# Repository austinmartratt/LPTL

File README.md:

# LPTL
Low Power Temperature Logger - Bluetooth Low Energy

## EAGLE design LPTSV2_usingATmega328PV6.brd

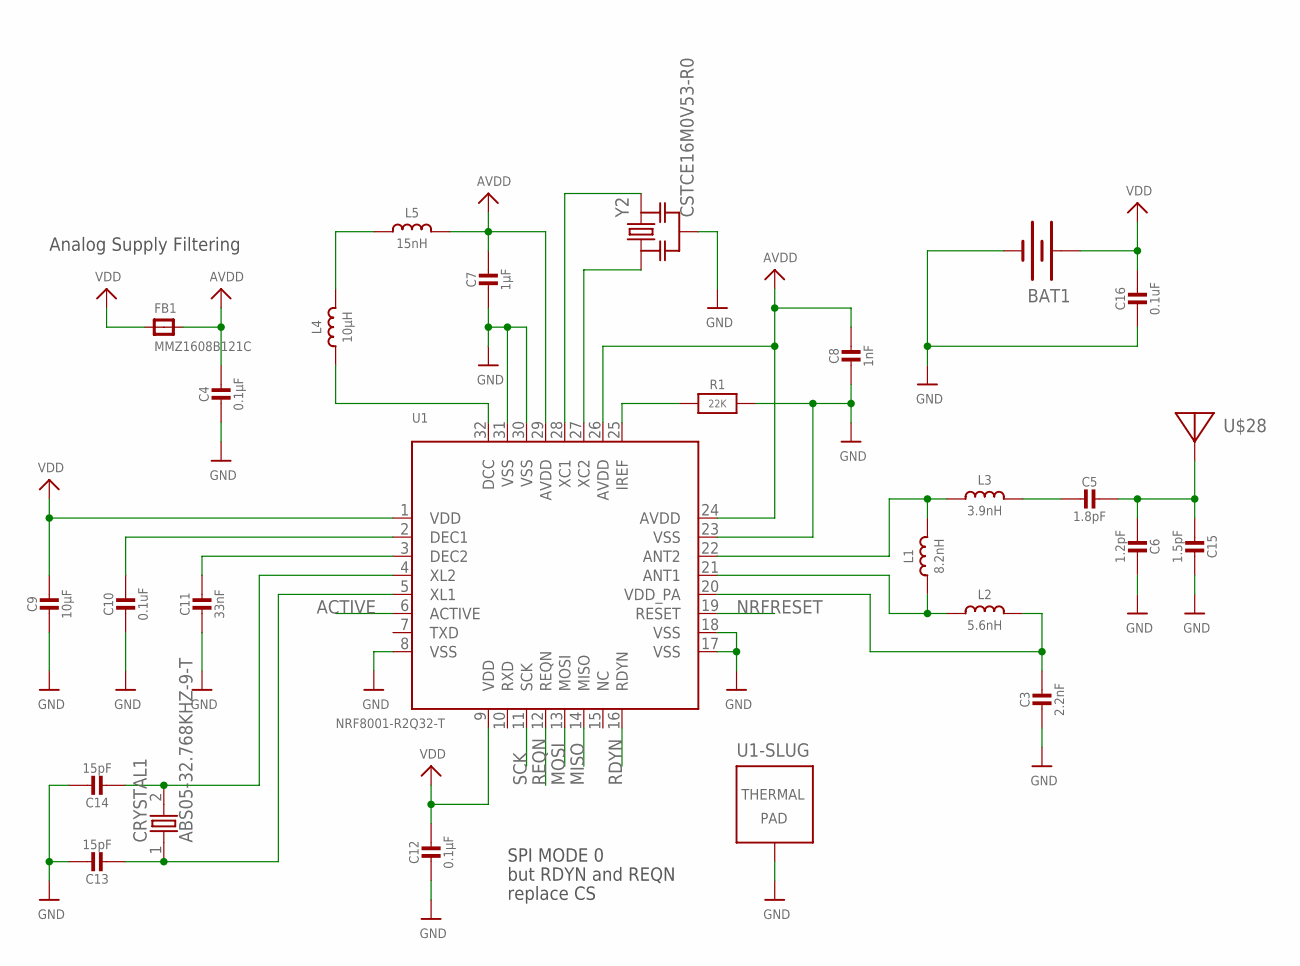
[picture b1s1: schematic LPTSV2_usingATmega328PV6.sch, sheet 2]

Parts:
BAT1: LINX-BAT-HLD-00120SMD; BATTCON_20MM; PARTNUMBER BAT-HLD-001-TRCT-ND
C3: 2.2nF; _0402; PARTNUMBER C0402C222J8JAC7867
C4, C12: 0.1µF; _0402; PARTNUMBER GRM155R71C104KA88J
C5: 1.8pF; _0402MP; PARTNUMBER GRM1555C1E1R8BA01D
C6: 1.2pF; _0402MP; PARTNUMBER GRM1555C1E1R2BA01D
C7: 1µF; _0402; PARTNUMBER 0402ZD105KAT2A
C8: 1nF; _0402; PARTNUMBER GRM155R71H102KA01D
C9: 10µF; _0402; PARTNUMBER GRM155R60J106ME15D
C10, C16: 0.1uF; _0402; PARTNUMBER GRM155R71C104KA88J
C11: 33nF; _0402; PARTNUMBER C0402C333K8RACTU
C13, C14: 15pF; _0402; PARTNUMBER GRM1555C1H150JA01D
C15: 1.5pF; _0402MP; PARTNUMBER GRM1555C1H1R5BA01D
CRYSTAL1: ABS05-32.768KHZ-9-T; CRYSTAL-2PIN
FB1: MMZ1608B121C; 0805; PARTNUMBER MMZ1608B121CTDH5
L1: 8.2nH; _0402; PARTNUMBER LQP15MN8N2B02D
L2: 5.6nH; _0402; PARTNUMBER LQP15MN5N6B02D
L3: 3.9nH; _0402; PARTNUMBER LQP03TN3N9B02D
L4: 10µH; _0603; PARTNUMBER LBMF1608T100K
L5: 15nH; _0603; PARTNUMBER L-14C15NJV4T
R1: 22K; _0805; PARTNUMBER RC0805JR-0722KL
U1: NRF8001-R2Q32-T; MICROBUILDER_QFN32_5MM
U$28: ANTENNA_PCBNRF8001_1.6MM; ANT_PCB_2.4GHZ_NRF8001_1.6MM_1OZ
Y2: CSTCE16M0V53-R0; RESONATOR_MURATA2

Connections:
ACTIVE: U1.6 (ACTIVE)
AVDD: C4.1, C7.1, C8.1, FB1.2, L5.2, U1.24 (AVDD), U1.26 (AVDD), U1.29 (AVDD)
GND: BAT1.2 (-), C3.2, C4.2, C6.1, C7.2, C8.2, C9.2, C10.2, C11.2, C12.2, C13.1, C14.1, C15.1, C16.2, R1.2, U1.8 (VSS), U1.17 (VSS), U1.18 (VSS), U1.23 (VSS), U1.30 (VSS), U1.31 (VSS), U1.33 (TP), Y2.2; also elsewhere on the board
MISO: U1.14 (MISO); also elsewhere on the board
MOSI: U1.13 (MOSI); also elsewhere on the board
unnamed: L1.2, L3.1, U1.22 (ANT2)
unnamed: L1.1, L2.1, U1.21 (ANT1)
unnamed: C3.1, L2.2, U1.20 (VDD_PA)
unnamed: L4.2, L5.1
unnamed: C5.2, L3.2
unnamed: C11.1, U1.3 (DEC2)
unnamed: C10.1, U1.2 (DEC1)
unnamed: U1.28 (XC1), Y2.3
unnamed: U1.27 (XC2), Y2.1
unnamed: L4.1, U1.32 (DCC)
unnamed: R1.1, U1.25 (IREF)
unnamed: C5.1, C6.2, C15.2, U$28.FEED
unnamed: C14.2, CRYSTAL1.2, U1.4 (XL2)
unnamed: C13.2, CRYSTAL1.1, U1.5 (XL1)
NRFRESET: U1.19 (RESET); also elsewhere on the board
RDYN: U1.16 (RDYN); also elsewhere on the board
REQN: U1.12 (REQN); also elsewhere on the board
SCK: U1.11 (SCK); also elsewhere on the board
VDD: BAT1.1 (+), BAT1.3 (+), C9.1, C12.1, C16.1, FB1.1, U1.1 (VDD), U1.9 (VDD); also elsewhere on the board

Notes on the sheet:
Analog Supply Filtering
SPI MODE 0
but RDYN and REQN
replace CS

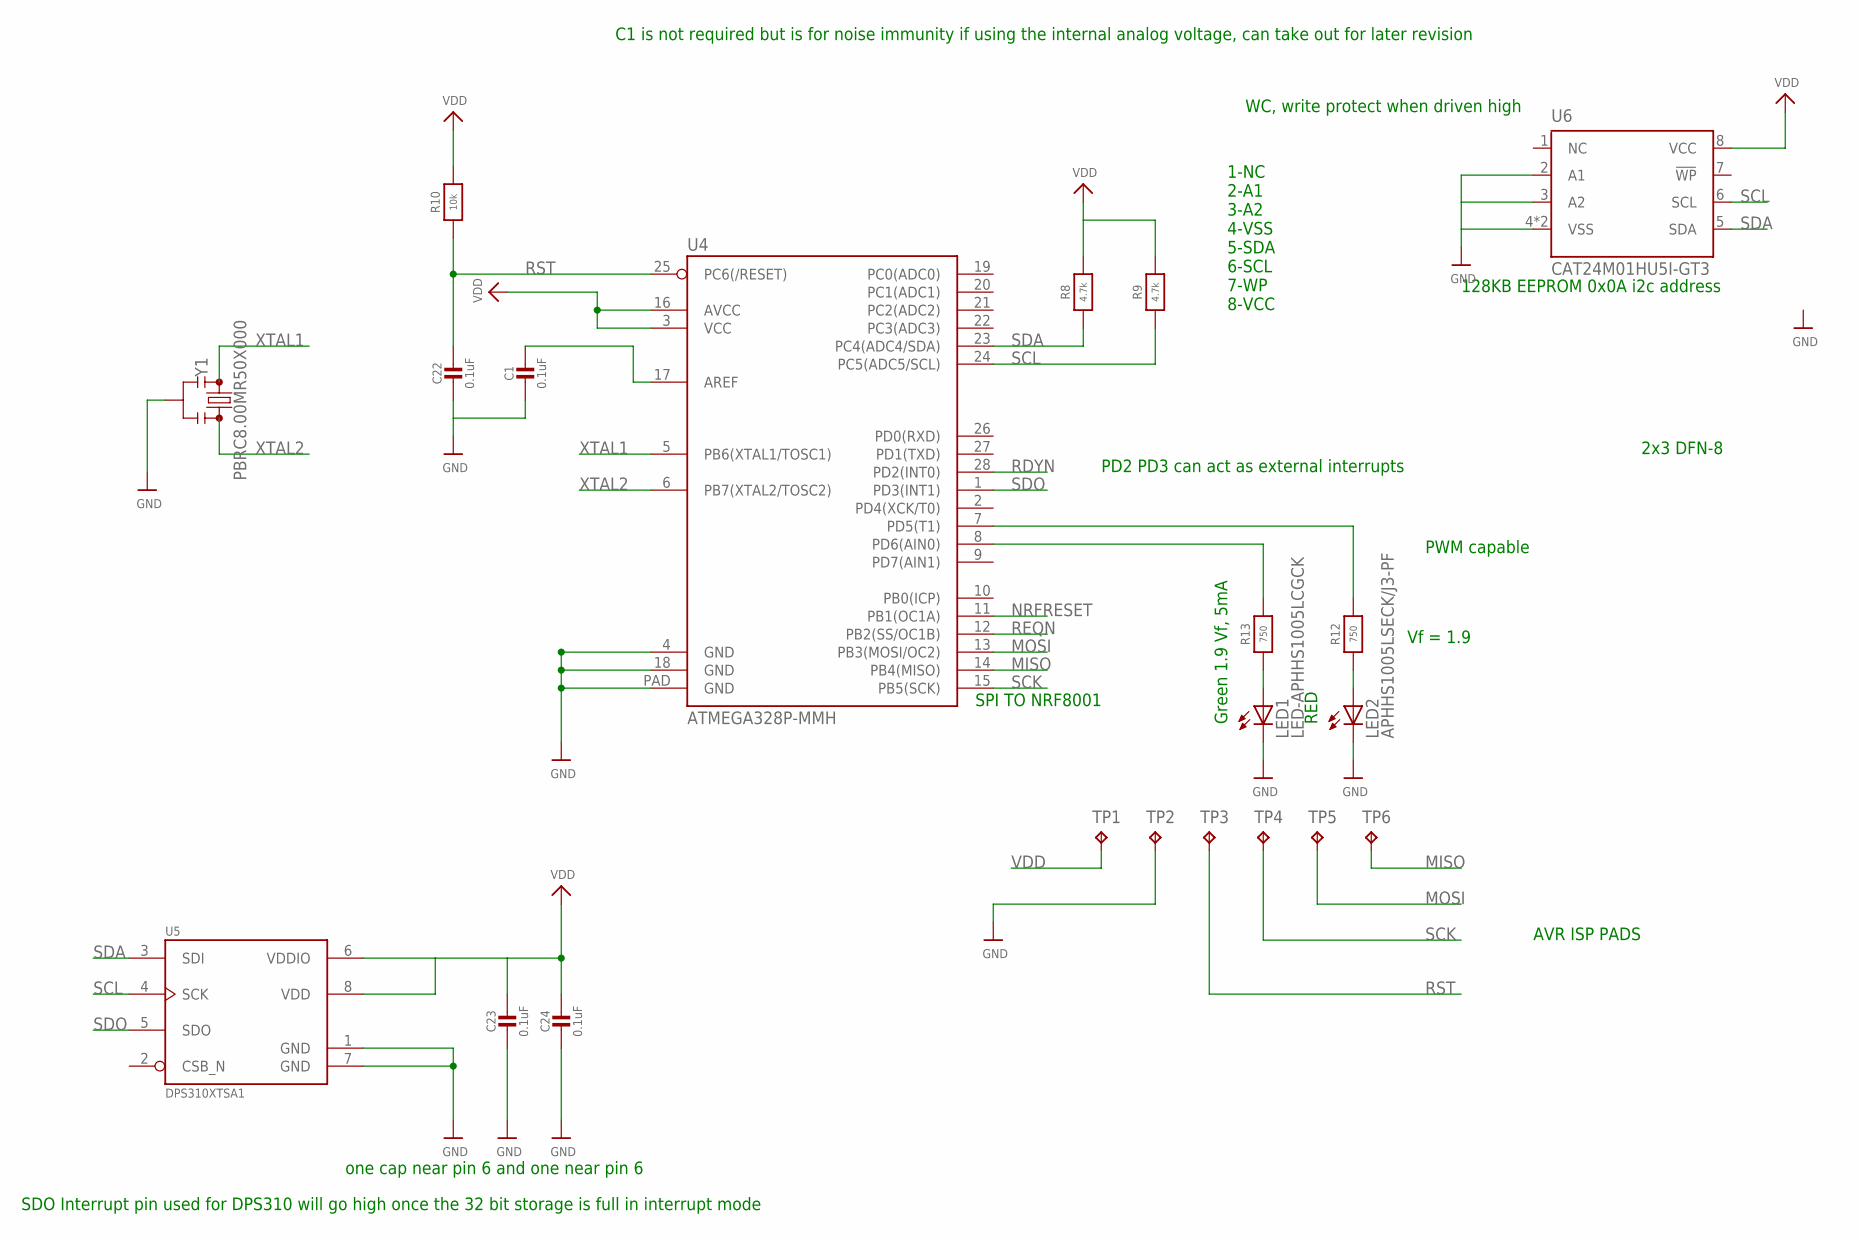
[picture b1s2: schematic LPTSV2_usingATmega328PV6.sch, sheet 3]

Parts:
C1, C22, C23, C24: 0.1uF; _0402; PARTNUMBER GRM155R71C104KA88J
LED1: LED-APHHS1005LCGCK; 0402-LED
LED2: APHHS1005LSECK/J3-PF; 0402-LED
R8, R9: 4.7k; _0402; PARTNUMBER RC0402JR-074K7L
R10: 10k; _0402; PARTNUMBER RC0402JR-0710KL
R12, R13: 750; _0402; PARTNUMBER RC0402JR-07750RL
TP1, TP2, TP3, TP4, TP5, TP6: TPTP10SQ; TP10SQ
U4: ATMEGA328P-MMH; SPARKFUN-IC-MICROCONTROLLER_VQFN-28
U5: DPS310XTSA1; LGA8S145X65P2X4_200X250X100
U6: CAT24M01HU5I-GT3; DFN-2X3
Y1: PBRC8.00MR50X000; RESONATOR-SMD-4.5X2.0

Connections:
GND: C1.2, C22.2, C23.2, C24.2, LED1.C, LED2.C, TP2.TP, U4.4 (GND), U4.18 (GND), U4.PAD (GND), U5.1 (GND), U5.7 (GND), U6.2 (A1), U6.3 (A2), U6.4 (VSS), U6.EXP (VSS), Y1.2; also elsewhere on the board
MISO: TP6.TP, U4.14 (PB4(MISO)); also elsewhere on the board
MOSI: TP5.TP, U4.13 (PB3(MOSI/OC2)); also elsewhere on the board
unnamed: R12.2, U4.7 (PD5(T1))
unnamed: R13.2, U4.8 (PD6(AIN0))
unnamed: LED1.A, R13.1
unnamed: LED2.A, R12.1
unnamed: C1.1, U4.17 (AREF)
NRFRESET: U4.11 (PB1(OC1A)); also elsewhere on the board
RDYN: U4.28 (PD2(INT0)); also elsewhere on the board
REQN: U4.12 (PB2(SS/OC1B)); also elsewhere on the board
RST: C22.1, R10.1, TP3.TP, U4.25 (PC6(/RESET))
SCK: TP4.TP, U4.15 (PB5(SCK)); also elsewhere on the board
SCL: R9.1, U4.24 (PC5(ADC5/SCL)), U5.4 (SCK), U6.6 (SCL)
SDA: R8.1, U4.23 (PC4(ADC4/SDA)), U5.3 (SDI), U6.5 (SDA)
SDO: U4.1 (PD3(INT1)), U5.5 (SDO)
VDD: C23.1, C24.1, R8.2, R9.2, R10.2, TP1.TP, U4.3 (VCC), U4.16 (AVCC), U5.6 (VDDIO), U5.8 (VDD), U6.8 (VCC); also elsewhere on the board
XTAL1: U4.5 (PB6(XTAL1/TOSC1)), Y1.1
XTAL2: U4.6 (PB7(XTAL2/TOSC2)), Y1.3

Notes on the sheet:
one cap near pin 6 and one near pin 6
SPI TO NRF8001
PD2 PD3 can act as external interrupts
SDO Interrupt pin used for DPS310 will go high once the 32 bit storage is full in interrupt mode
Green 1.9 Vf, 5mA
RED
AVR ISP PADS
PWM capable
C1 is not required but is for noise immunity if using the internal analog voltage, can take out for later revision
Vf = 1.9
2x3 DFN-8
1-NC 2-A1 3-A2 4-VSS 5-SDA 6-SCL 7-WP 8-VCC
WC, write protect when driven high
128KB EEPROM 0x0A i2c address

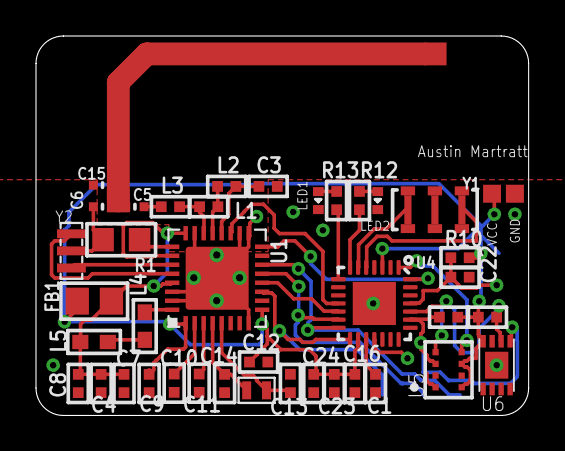
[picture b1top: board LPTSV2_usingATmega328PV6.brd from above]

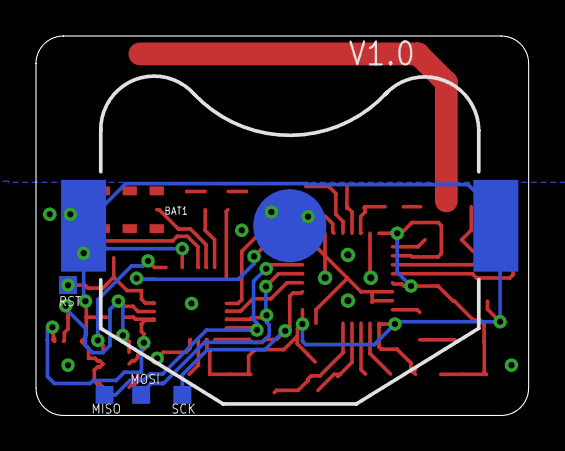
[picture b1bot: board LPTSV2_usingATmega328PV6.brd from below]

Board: 2 copper layers, 27.4 x 21.1 mm, 47 parts (5 on the bottom side), 34 nets.

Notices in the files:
parts and their libraries:
microbuilder: This work is placed in the public domain, and may be freely used for commercial and non-commercial work with the following conditions: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
SparkFun-Batteries: Licensing: Creative Commons ShareAlike 4.0 International - https://creativecommons.org/licenses/by-sa/4.0
